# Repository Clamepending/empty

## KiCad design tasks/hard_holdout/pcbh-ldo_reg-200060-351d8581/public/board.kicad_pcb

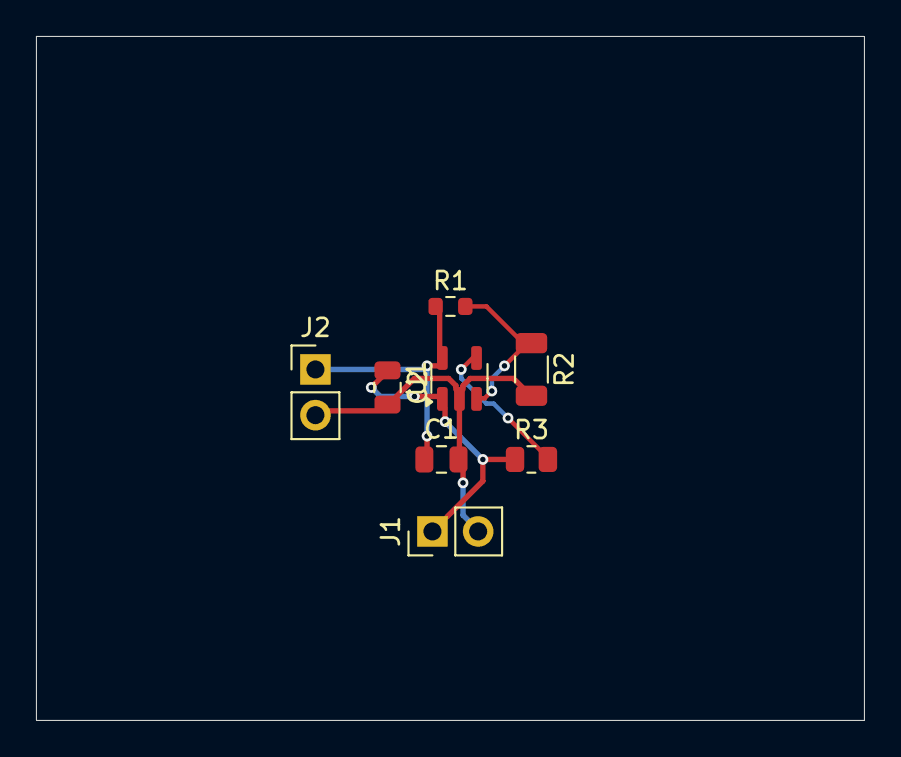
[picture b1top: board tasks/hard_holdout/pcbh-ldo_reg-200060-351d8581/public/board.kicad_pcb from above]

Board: 2 copper layers, 46.0 x 38.0 mm, 8 parts (0 on the bottom side), 5 nets.

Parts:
C1: 2.2u; C_0805_2012Metric
C2: 4.7u; C_0805_2012Metric
J1, J2: PinHeader_1x02_P2.54mm_Vertical
R1: 45.3k; R_0603_1608Metric
R2: 36.5; R_1206_3216Metric
R3: 15k; R_0805_2012Metric
U1: SOT-23-5

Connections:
+1V8: C1.1, J2.1, R1.1, U1.5
EN: R3.2, U1.4
FB: R1.2, R2.1, U1.3
GND: C1.2, C2.2, J1.2, J2.2, R2.2, U1.2
VIN: C2.1, J1.1, R3.1, U1.1

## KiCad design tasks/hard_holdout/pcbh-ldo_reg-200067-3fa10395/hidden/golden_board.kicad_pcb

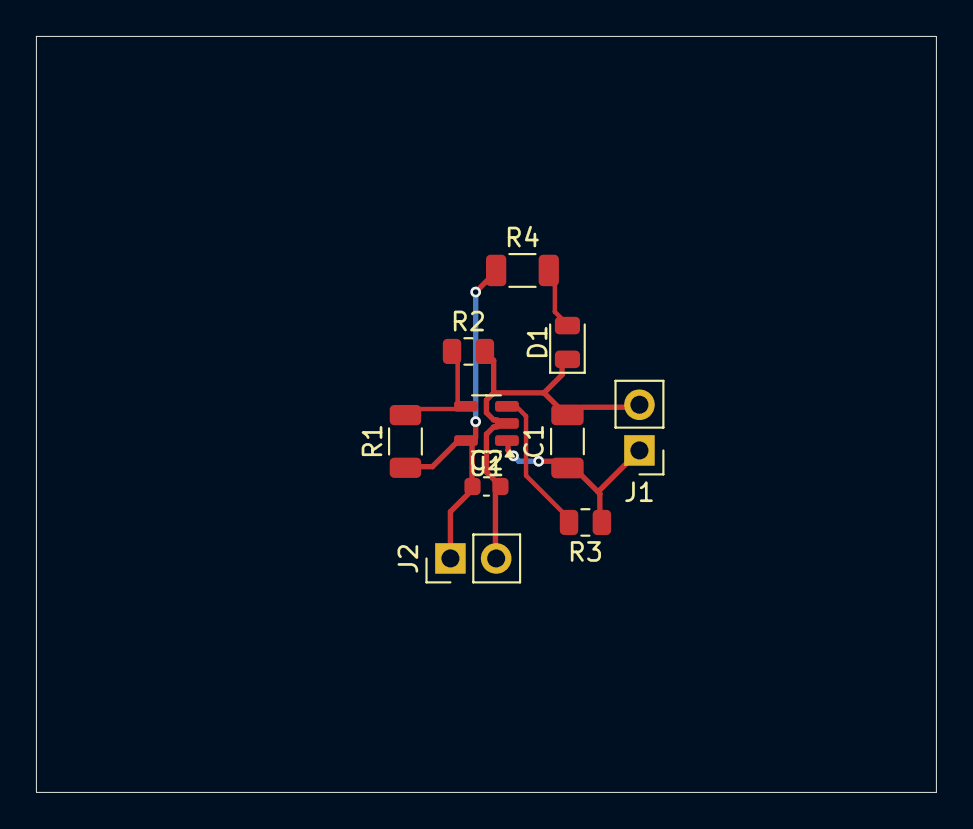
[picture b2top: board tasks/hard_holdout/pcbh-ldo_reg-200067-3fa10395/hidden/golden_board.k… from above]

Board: 2 copper layers, 50.0 x 42.0 mm, 10 parts (0 on the bottom side), 6 nets.

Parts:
C1: 1u; C_1206_3216Metric
C2: 1u; C_0603_1608Metric
D1: LED_0805_2012Metric
J1, J2: PinHeader_1x02_P2.54mm_Vertical
R1: 143k; R_1206_3216Metric
R2: 27.4k; R_0805_2012Metric
R3: 15k; R_0805_2012Metric
R4: 3k; R_1206_3216Metric
U1: SOT-23-5

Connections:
+5V: C2.1, J2.1, R1.1, R4.1, U1.5
EN: R3.2, U1.3
FB: R1.2, R2.1, U1.4
GND: C1.2, C2.2, D1.1, J1.2, J2.2, R2.2, U1.2
LED: D1.2, R4.2
VIN: C1.1, J1.1, R3.1, U1.1

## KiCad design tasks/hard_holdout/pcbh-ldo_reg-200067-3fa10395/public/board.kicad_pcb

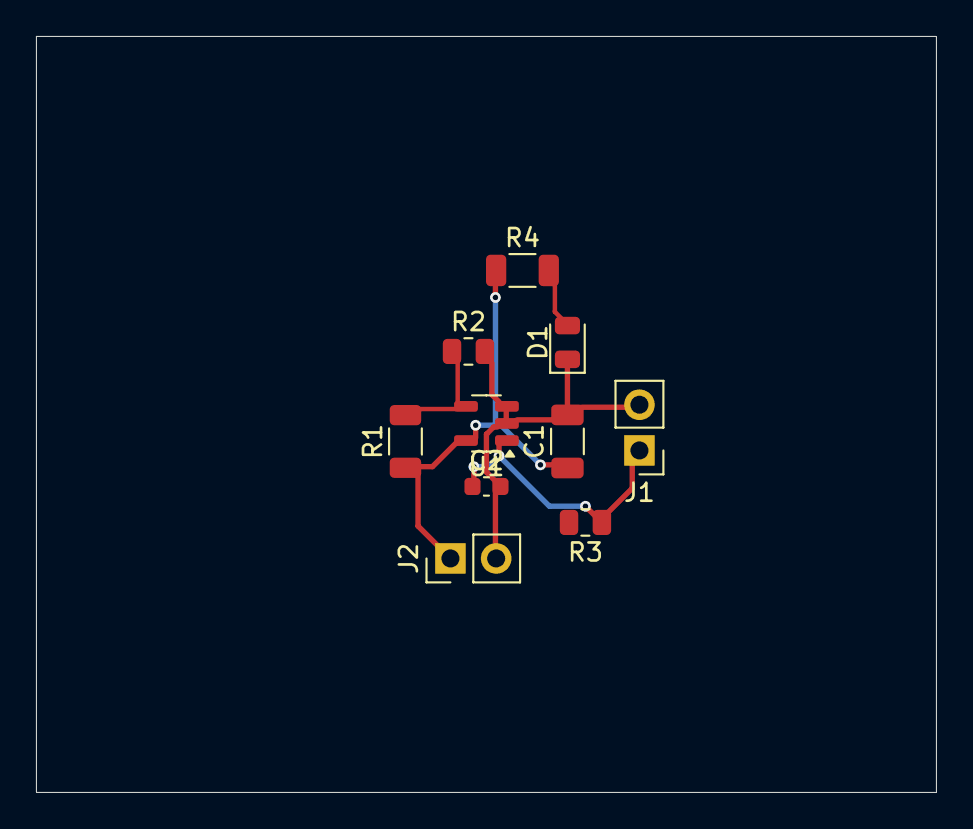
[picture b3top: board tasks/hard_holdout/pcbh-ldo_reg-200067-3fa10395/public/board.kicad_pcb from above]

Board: 2 copper layers, 50.0 x 42.0 mm, 10 parts (0 on the bottom side), 5 nets.

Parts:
C1: 1u; C_1206_3216Metric
C2: 1u; C_0603_1608Metric
D1: LED_0805_2012Metric
J1, J2: PinHeader_1x02_P2.54mm_Vertical
R1: 27.4k; R_1206_3216Metric
R2: 143k; R_0805_2012Metric
R3: 15k; R_0805_2012Metric
R4: 3k; R_1206_3216Metric
U1: SOT-23-5

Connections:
+5V: C1.1, J2.1, R1.1, R4.1, U1.5
FB: R1.2, R2.1, U1.4
GND: C1.2, C2.2, D1.1, J1.2, J2.2, R2.2, U1.2, U1.3
LED: D1.2, R4.2
VIN: C2.1, J1.1, R3.1, U1.1

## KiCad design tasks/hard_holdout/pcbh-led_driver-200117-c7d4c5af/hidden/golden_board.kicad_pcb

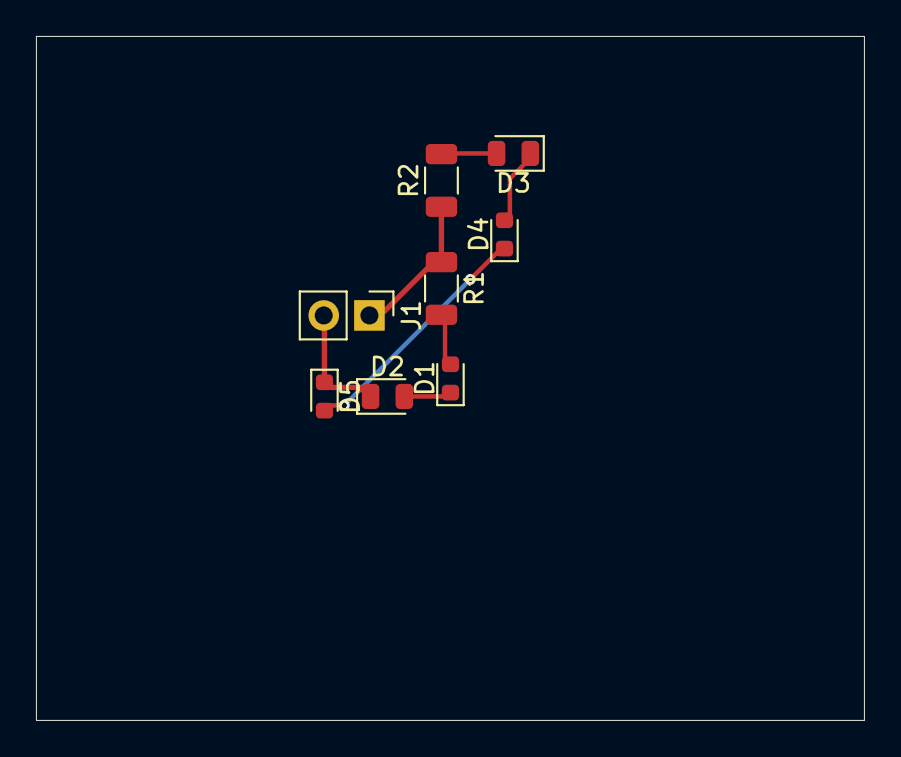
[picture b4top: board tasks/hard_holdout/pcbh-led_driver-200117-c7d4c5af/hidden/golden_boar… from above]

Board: 2 copper layers, 46.0 x 38.0 mm, 8 parts (0 on the bottom side), 7 nets.

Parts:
D1, D4, D5: LED_0603_1608Metric
D2, D3: LED_0805_2012Metric
J1: PinHeader_1x02_P2.54mm_Vertical
R1: 510; R_1206_3216Metric
R2: 390; R_1206_3216Metric

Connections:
CH1_0: D1.2, R1.2
CH1_1: D1.1, D2.2
CH2_0: D3.2, R2.2
CH2_1: D3.1, D4.2
CH2_2: D4.1, D5.2
GND: D2.1, D5.1, J1.2
VS: J1.1, R1.1, R2.1

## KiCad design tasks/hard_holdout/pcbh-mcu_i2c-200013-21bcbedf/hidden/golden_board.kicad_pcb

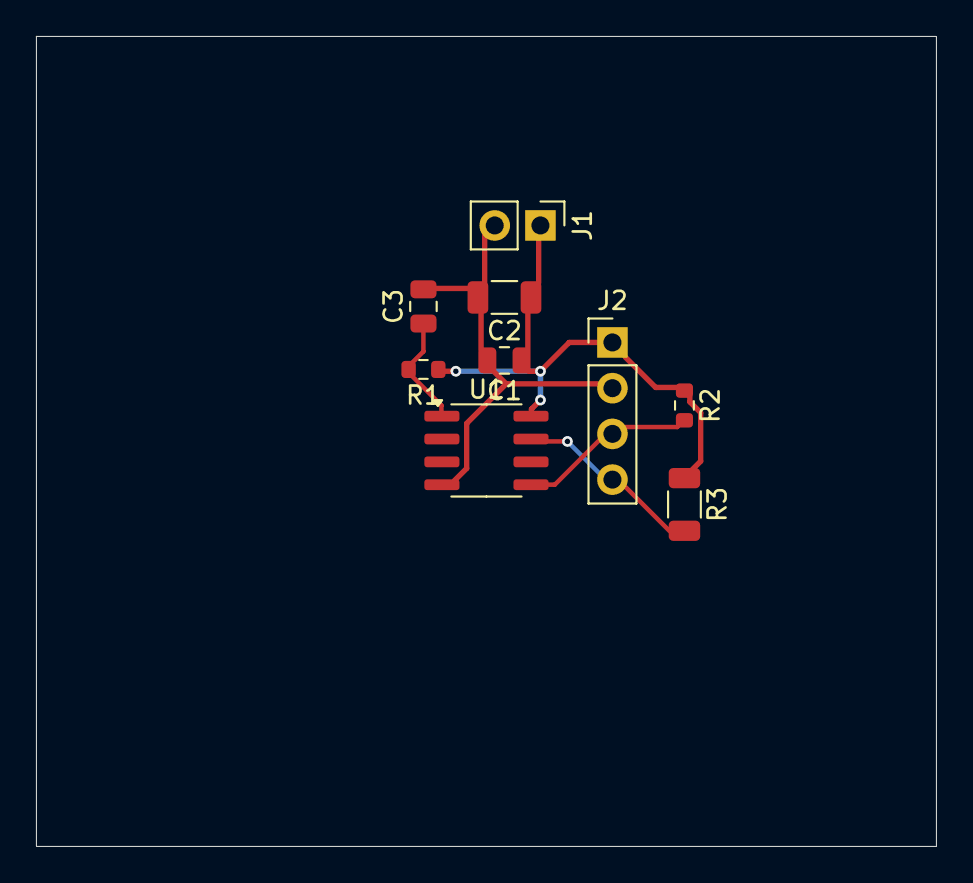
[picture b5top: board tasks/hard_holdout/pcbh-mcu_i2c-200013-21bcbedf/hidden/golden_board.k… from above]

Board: 2 copper layers, 50.0 x 45.0 mm, 9 parts (0 on the bottom side), 5 nets.

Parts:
C1, C3: 100n; C_0805_2012Metric
C2: 10u; C_1206_3216Metric
J1: PinHeader_1x02_P2.54mm_Vertical
J2: PinHeader_1x04_P2.54mm_Vertical
R1: 5.1k; R_0603_1608Metric
R2: 1.5k; R_0603_1608Metric
R3: 1.5k; R_1206_3216Metric
U1: SOIC-8_3.9x4.9mm_P1.27mm

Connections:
+1V8: C1.1, C2.1, J1.1, J2.1, R1.1, R2.1, R3.1, U1.8
GND: C1.2, C2.2, C3.2, J1.2, J2.2, U1.4
NRST: C3.1, R1.2, U1.1
SCL: J2.4, R3.2, U1.7
SDA: J2.3, R2.2, U1.5

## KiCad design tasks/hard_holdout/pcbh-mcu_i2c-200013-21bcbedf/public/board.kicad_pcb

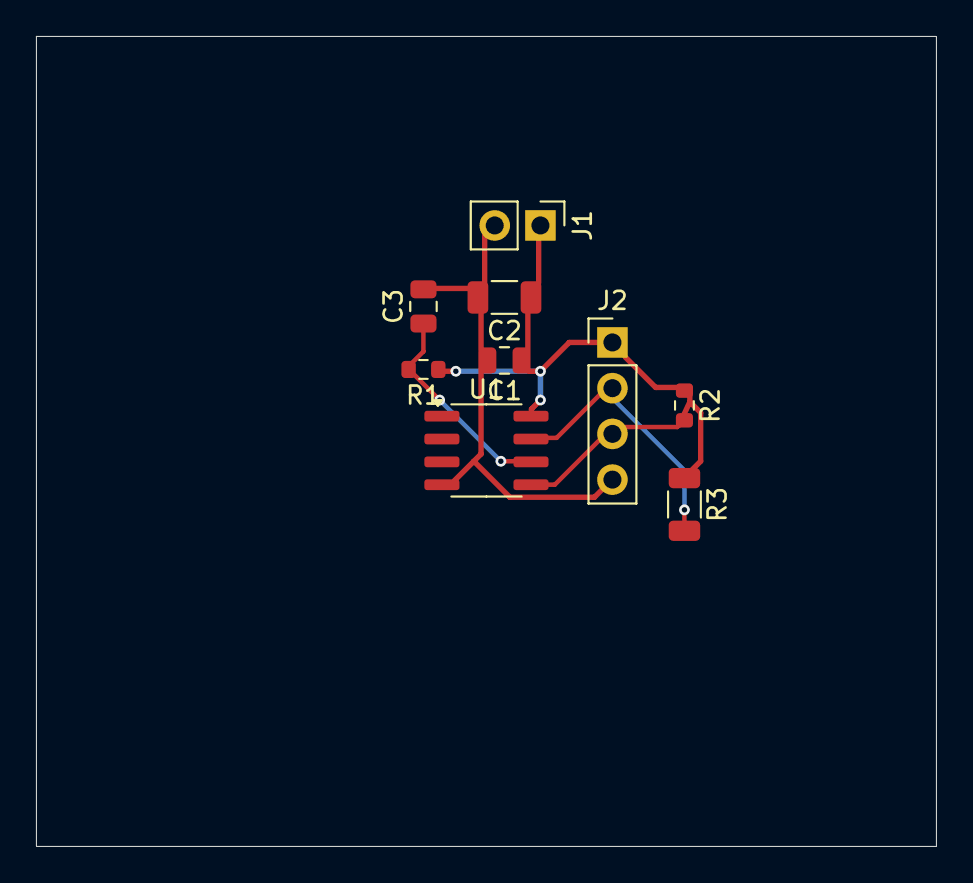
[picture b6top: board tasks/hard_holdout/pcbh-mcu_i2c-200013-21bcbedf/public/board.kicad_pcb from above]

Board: 2 copper layers, 50.0 x 45.0 mm, 9 parts (0 on the bottom side), 5 nets.

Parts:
C1, C3: 100n; C_0805_2012Metric
C2: 10u; C_1206_3216Metric
J1: PinHeader_1x02_P2.54mm_Vertical
J2: PinHeader_1x04_P2.54mm_Vertical
R1: 5.1k; R_0603_1608Metric
R2: 1.5k; R_0603_1608Metric
R3: 1.5k; R_1206_3216Metric
U1: SOIC-8_3.9x4.9mm_P1.27mm

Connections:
+1V8: C1.1, C2.1, J1.1, J2.1, R1.1, R2.1, R3.1, U1.8
GND: C1.2, C2.2, C3.2, J1.2, J2.4, U1.4
NRST: C3.1, R1.2, U1.6
SCL: J2.2, R3.2, U1.7
SDA: J2.3, R2.2, U1.5
